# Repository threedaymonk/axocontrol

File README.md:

# Axoloti control board

A control board for the [Axoloti Core](http://www.axoloti.com/) board.

Inspired by [Tom Whitwell's Axo
Control](https://github.com/TomWhitwell/Axo-Control), but adds a rotary encoder
and an I2C OLED screen and removes the joystick.

## Features:

- 8 potentiometers
- Rotary encoder with switch
- 3 push buttons
- 3 LEDs (below buttons)
- OLED screen

## Bill of materials

| Qty | Ref | Part | Notes  |
| --- | --- | ---- | ------ |
|   8 | RV1-8 | 9mm potentiometer B10k | [Thonk](https://www.thonk.co.uk/shop/alpha-9mm-pots-dshaft/) |
|   3 | SW1-3 | C&K tactile switch | [Thonk](https://www.thonk.co.uk/shop/radio-music-switch/) |
|   1 | SW4 | Encoder with switch | [Bourns PEC11R-4220F-S0024](https://www.mouser.co.uk/ProductDetail/Bourns/PEC11R-4220F-S0024) matches the above potentiometers in height |
|  10 | C1-9 | Capacitor 0603 100n | Might not be needed, can also try 10n for C9 and C10 |
|   3 | R1-3 | Resistor 0603 1k | |
|   2 | R5, R6 | Resistor 0603 10k | |
|   3 | D1-3 | 3mm LED | |
|   1 | | 0.96" White I2C SSD1306 OLED | Pin order VCC GND SCL SDA, e.g. [Banggood](https://uk.banggood.com/5Pcs-0_96-Inch-4Pin-White-IIC-I2C-OLED-Display-Module-12864-LED-p-971295.html) |
|   1 | | 1×40 2.54mm header | |
|   1 | | 1×40 2.54mm socket | |
|   1 | | 1900H knob without line | [Thonk](https://www.thonk.co.uk/shop/1900h-d/) |
|   8 | | 1900H knob with line | [Thonk](https://www.thonk.co.uk/shop/1900h-d/) |
|   8 | | 1.4mm dia × 4mm screw for plastic | For mounting screen: [Bitsbox](https://www.bitsboxuk.com/index.php?main_page=product_info&cPath=238_241&products_id=3443) |
|   6 | | M3 × 8mm screw | |
|   6 | | M3 × 11mm threaded standoff | |

## Hardware

OpenSCAD files for hardware are provided:

- axo-base.scad: lower part of enclosure
- axo-top.scad: upper part of enclosure
- ssd1306-riser.scad: riser for the display to bring it to the same height as
  the controls, so that it sits just below the front panel

## Connections

    OLED       ENC      RV1  RV2  RV3  RV4
    SDA PB9    SW PB6   PC3  PC4  PA0  PB1
    SCL PB8    A  PB7
               B  PC0

    SW1   SW2   SW3     RV5  RV6  RV7  RV8
    PC1   PC2   PC5     PA4  PA6  PA7  PB0

    LED1  LED2  LED3
    PA1   PA2   PA3

## Reuse

<br />This work is licensed under a <a rel="license" href="http://creativecommons.org/licenses/by-sa/4.0/">Creative Commons Attribution-ShareAlike 4.0 International License</a>.

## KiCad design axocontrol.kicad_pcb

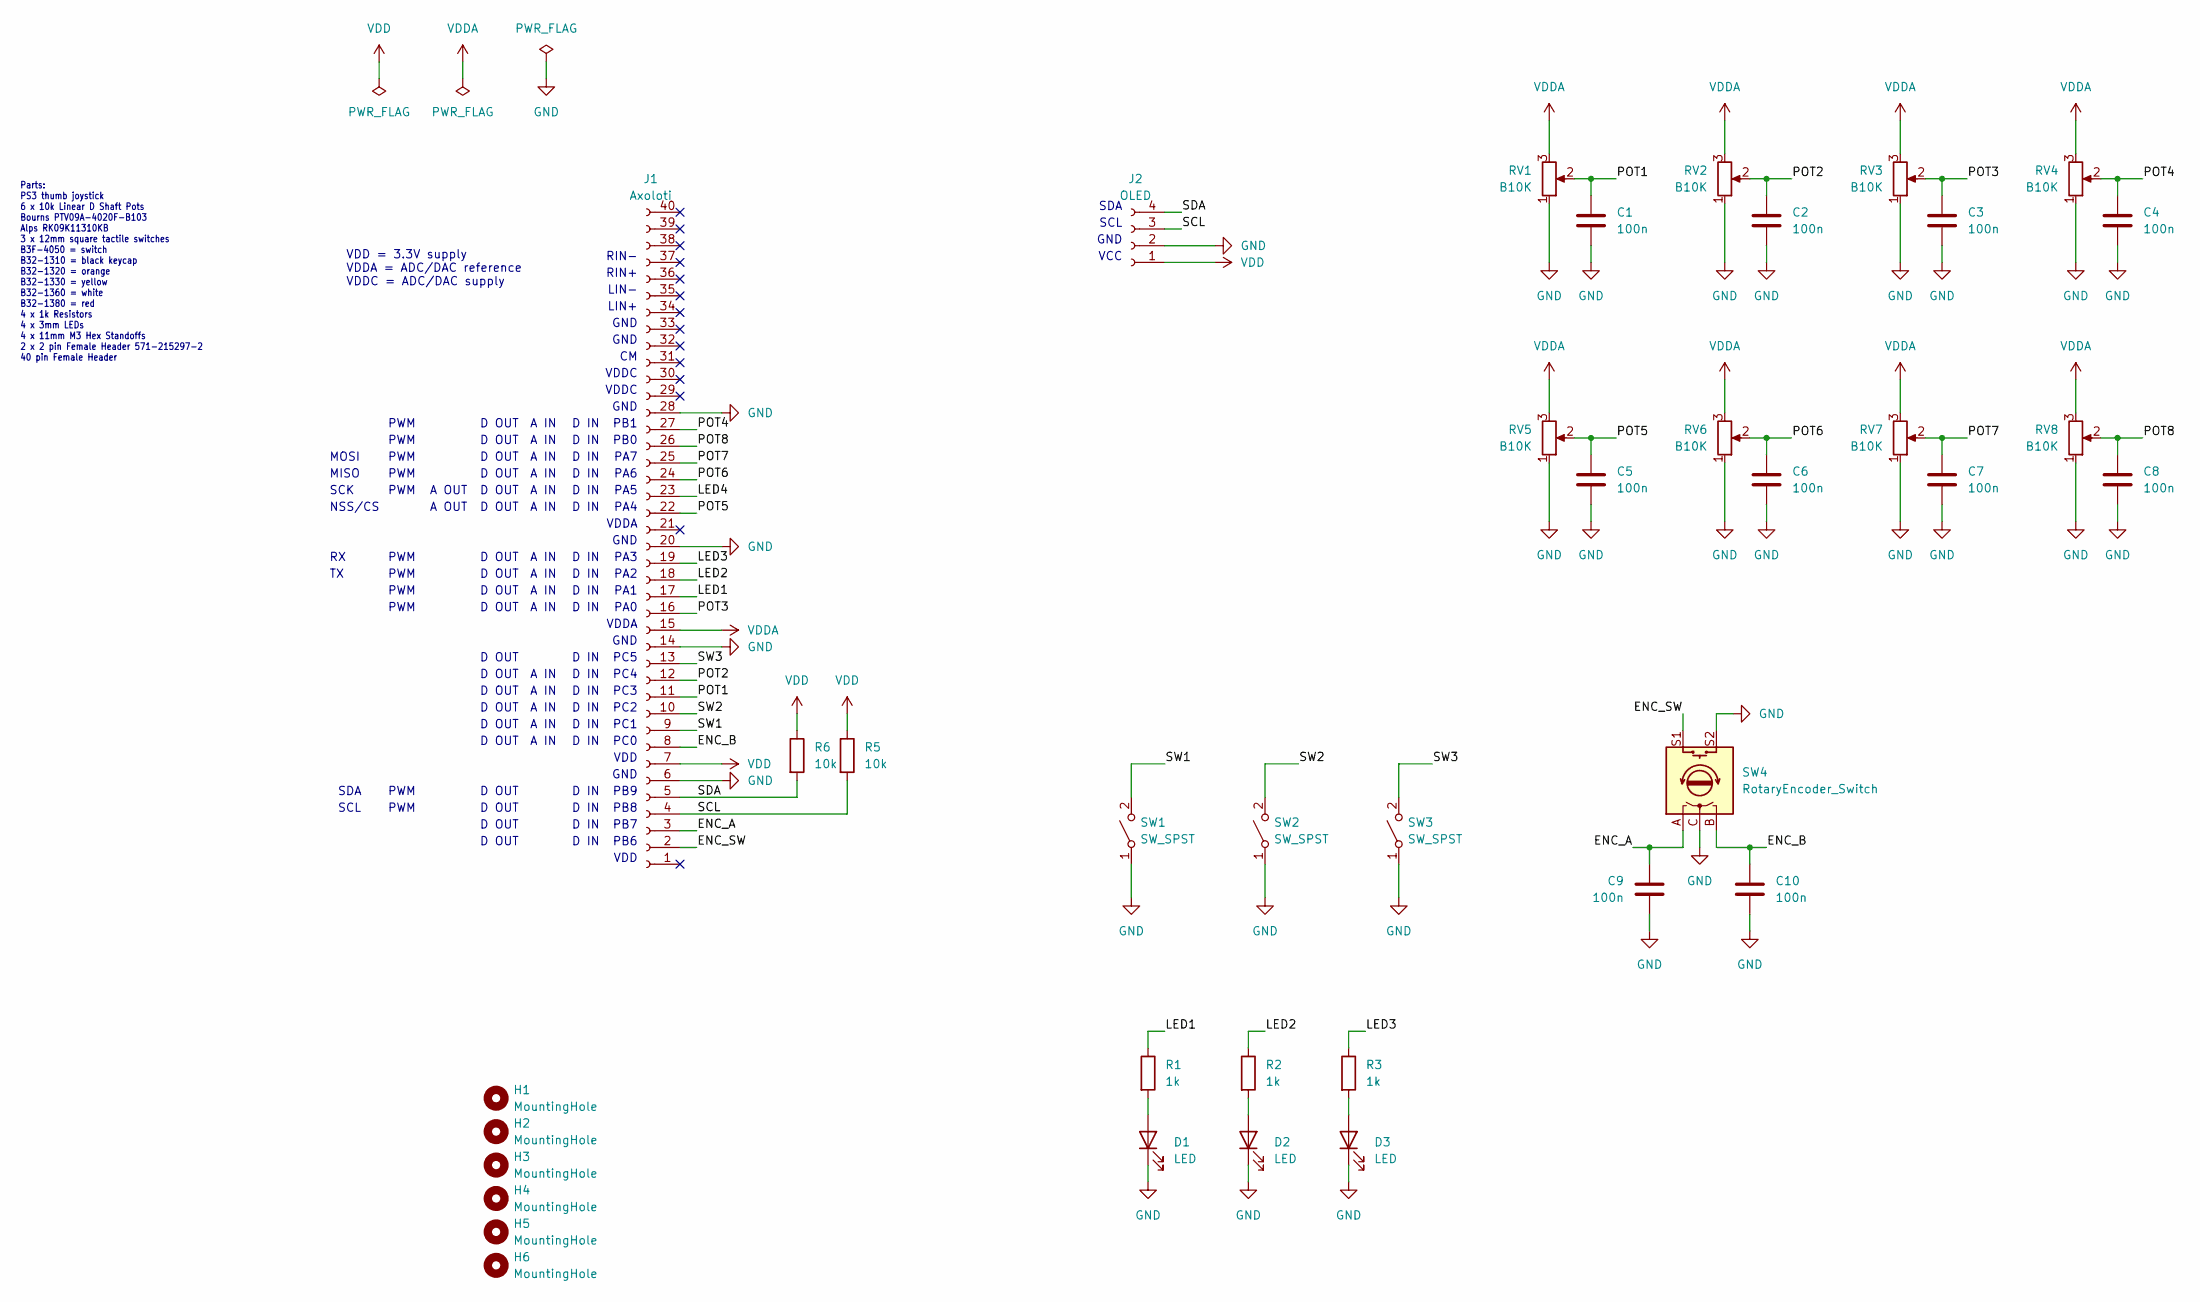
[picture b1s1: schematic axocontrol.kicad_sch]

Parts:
C1, C2, C3, C4, C5, C6, C7, C8, C9, C10: 100n; C_0603_1608Metric_Pad1.08x0.95mm_HandSolder
D1, D2, D3: LED; LED_D3.0mm
H1, H2, H3, H4, H5, H6: MountingHole; MountingHole_3mm
J1: Axoloti; PinSocket_1x40_P2.54mm_Vertical
J2: OLED; OLED_128x64
R1, R2, R3: 1k; R_0603_1608Metric_Pad0.98x0.95mm_HandSolder
R5, R6: 10k; R_0603_1608Metric_Pad0.98x0.95mm_HandSolder
RV1, RV2, RV3, RV4, RV5, RV6, RV7, RV8: B10K; Alpha_9mm_Pot
SW1, SW2, SW3: SW_SPST; CK_D6R90_Push_Switch_SPST
SW4: RotaryEncoder_Switch; Bourns_PEC11R_Encoder_Switch; Mouser 652-PEC11R-4220F-S24

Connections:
/ENC_A: C9.1, J1.3, SW4.A
/ENC_B: C10.1, J1.8, SW4.B
/ENC_SW: J1.2, SW4.S1
/LED1: J1.17, R1.1
/LED2: J1.18, R2.1
/LED3: J1.19, R3.1
/LED4: J1.23
/POT1: C1.1, J1.11, RV1.2; also elsewhere on the board
/POT2: C2.1, J1.12, RV2.2
/POT3: C3.1, J1.16, RV3.2
/POT4: C4.1, J1.27, RV4.2
/POT5: C5.1, J1.22, RV5.2
/POT6: C6.1, J1.24, RV6.2
/POT7: C7.1, J1.25, RV7.2; also elsewhere on the board
/POT8: C8.1, J1.26, RV8.2
/SCL: J1.4, J2.3, R5.2
/SDA: J1.5, J2.4, R6.2
/SW1: J1.9, SW1.2 (B)
/SW2: J1.10, SW2.2 (B)
/SW3: J1.13, SW3.2 (B)
GND: C1.2, C2.2, C3.2, C4.2, C5.2, C6.2, C7.2, C8.2, C9.2, C10.2, D1.1 (K), D2.1 (K), D3.1 (K), J1.6, J1.14, J1.20, J1.28, J2.2, RV1.1, RV2.1, RV3.1, RV4.1, RV5.1, RV6.1, RV7.1, RV8.1, SW1.1 (A), SW2.1 (A), SW3.1 (A), SW4.C, SW4.S2; also elsewhere on the board
unnamed: D1.2 (A), R1.2
unnamed: D2.2 (A), R2.2
unnamed: D3.2 (A), R3.2
VDD: J1.7, J2.1, R5.1, R6.1
VDDA: J1.15, RV1.3, RV2.3, RV3.3, RV4.3, RV5.3, RV6.3, RV7.3, RV8.3; also elsewhere on the board

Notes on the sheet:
PB8
PWM
D OUT
MISO
A IN
D IN
RIN+
PA4
PA5
PB0
PB1
NSS/CS
VDDA
PA7
PB9
PA0
MOSI
PC1
SDA
PC5
VDD = 3.3V supply VDDA = ADC/DAC reference VDDC = ADC/DAC supply
GND
PA3
VDDC
Parts: PS3 thumb joystick 6 x 10k Linear D Shaft Pots Bourns PTV09A-4020F-B103 Alps RK09K11310KB 3 x 12mm square tactile switches B3F-4050 = switch B32-1310 = black keycap B32-1320 = orange B32-1330 = yellow B32-1360 = white B32-1380 = red 4 x 1k Resistors 4 x 3mm LEDs 4 x 11mm M3 Hex Standoffs 2 x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
VDD
PA2
SCL
SCK
PC4
PA1
A OUT
LIN+
LIN-
PB7
PB6
PA6
PC0
PC2
RIN-

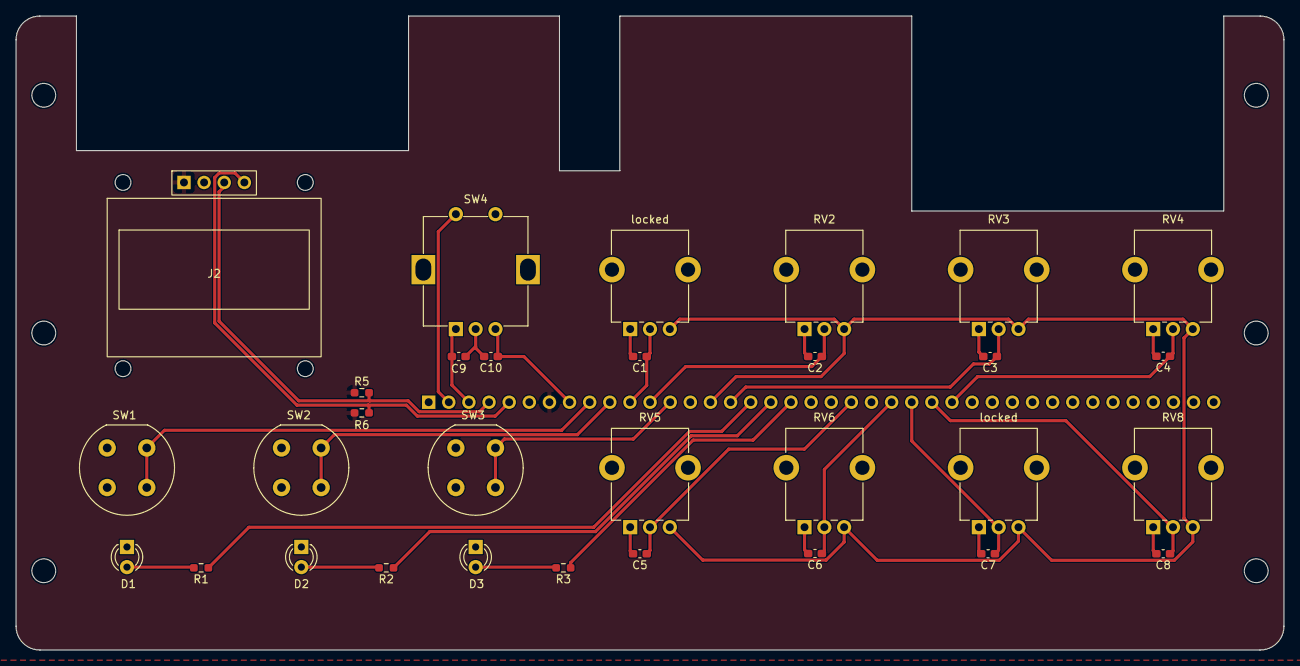
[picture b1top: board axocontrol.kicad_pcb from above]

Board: 2 copper layers, 160.0 x 80.0 mm, 38 parts (1 on the bottom side), 25 nets.

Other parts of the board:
locked: B10K; Alpha_9mm_Pot
locked#2: B10K; Alpha_9mm_Pot
locked#3: MountingHole; MountingHole_3mm

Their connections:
/POT1: locked.2; also elsewhere on the board
/POT7: locked#2.2; also elsewhere on the board
GND: locked.1, locked#2.1; also elsewhere on the board
VDDA: locked.3, locked#2.3; also elsewhere on the board

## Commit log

2022-01-13 Initial empty commit
2023-01-08 Initial PCB
2023-01-08 Move rounded rectangle to shared library
    It's called rounded_square for consistency.
2023-01-08 Ignore stl files
2023-01-08 Increase gap on sides for easier fitting
    The barrel connector was very tight.
2023-01-08 Include headphone socket in merged slot
2023-01-08 Enlarge gap around MIDI connectors
    The plugs wouldn't fit.
2023-01-08 Give top plate 3mm margin
    Also tweak screen position and reduce struts for quicker printing.
2023-01-08 Rename models for easier printing
2023-01-08 Enlarge window to fit OLED
2023-01-08 Model for case
2023-01-08 Remove acrylic
2023-01-08 Show model of board on preview
    Model from https://github.com/Believotron/3D-Models
2023-01-08 Ignore all JLCPCB files
2023-01-08 Tweak spacer
    This also adds a front-to-back strut to stop flexing in the y axis.
2023-01-08 Use blind threaded inserts
    This makes the top panel nicer and simplifies assembly as everything can
    be screwed to the top plate.
2023-01-08 Tweak feet and power cutout
2023-01-08 Add spacer/upper reinforcement
2023-01-08 Add front plate to spacer
    Laser cut acrylic is expensive, so let's not!
2023-01-08 Allow for paint around OLED
2023-01-08 Build in parallel
2023-01-08 Use bosses developed for top
2023-01-08 Generate top panel
    This needs manual tweaking in Inkscape, so the file generated is
    ignored in git.
2023-01-08 Correct manifold of boss
2023-01-08 Make LED exact
    These can be finished with a drill.
2023-01-08 Add riser for screen
2023-01-08 Finish documenting
2023-01-08 Add LEDs
